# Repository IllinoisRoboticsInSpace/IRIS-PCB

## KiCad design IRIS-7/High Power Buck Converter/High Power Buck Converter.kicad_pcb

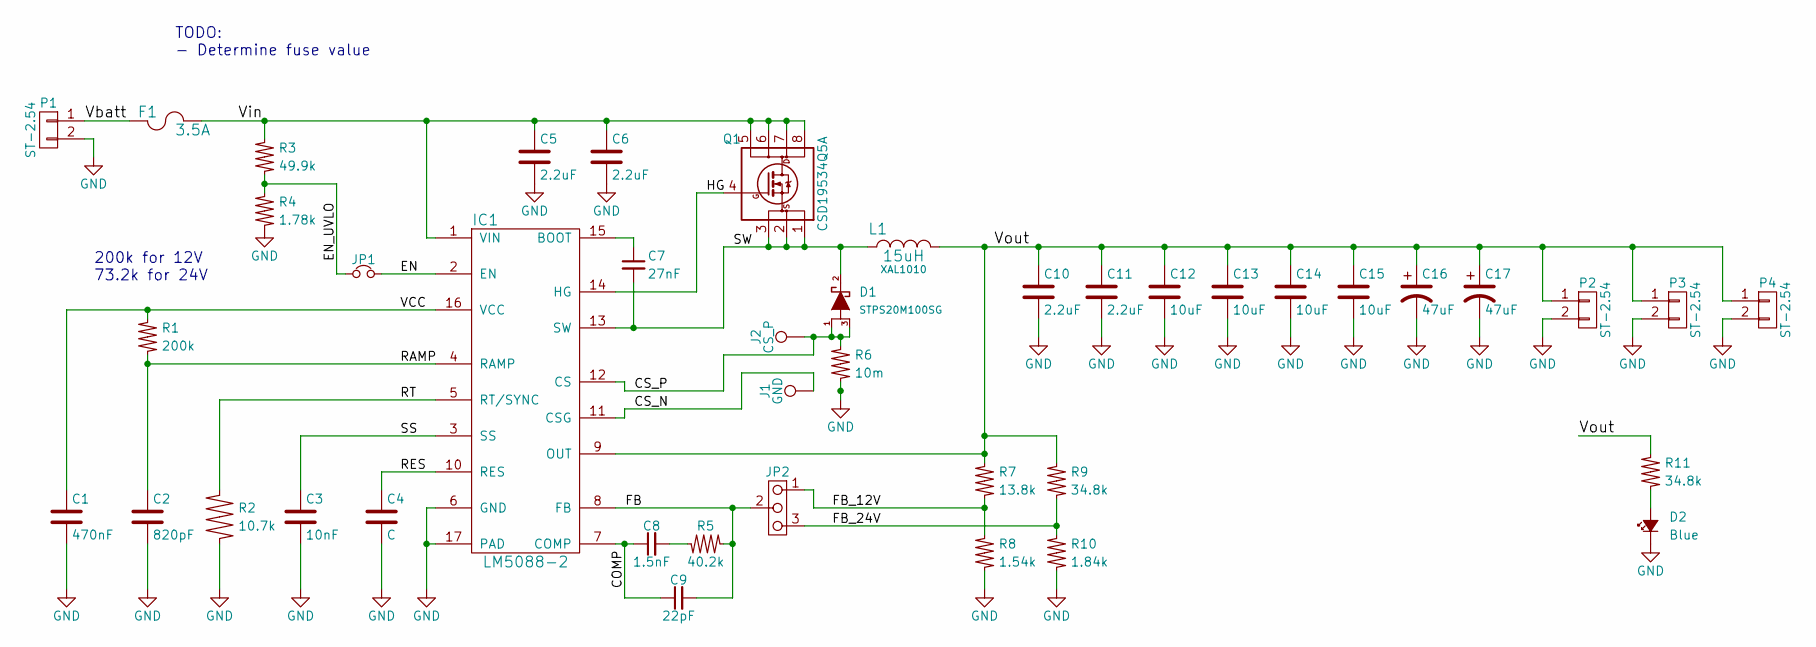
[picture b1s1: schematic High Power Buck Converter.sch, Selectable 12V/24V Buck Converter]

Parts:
C1: 470nF; C_0805
C2: 820pF; C_0805
C3: 10nF; C_0805
C4: C; C_0805
C5, C6, C10, C11: 2.2uF; C_1210
C7: 27nF; C_0805
C8: 1.5nF; C_0805
C9: 22pF; C_0805
C12, C13, C14, C15: 10uF; C_1206
C16, C17: 47uF; CP_Elec_8x10.5
D1: STPS20M100SG; TO-263-3Lead
D2: Blue; LED_0805
F1: 3.5A; Fuseholder5x20_horiz_open_Schurter_0031_8201
IC1: LM5088-2; HTSSOP-16_EP
J1: GND; SMD_0.3
J2: CS_P; SMD_0.3
JP1: JP_NC; Pin_Header_Straight_1x02_Pitch2.54mm
JP2: JP-3_R; Pin_Header_Straight_1x03_Pitch2.54mm
L1: 15uH; XAL1010
P1, P2, P3, P4: ST-2.54; TerminalBlock_Pheonix_MKDS1.5-2pol
Q1: CSD19534Q5A; TDSON-8-1
R1: 200k; R_0805
R2: 10.7k; R_0805
R3: 49.9k; R_0805
R4: 1.78k; R_0805
R5: 40.2k; R_0805
R6: 10m; R_2010
R7: 13.8k; R_0805
R8: 1.54k; R_0805
R9, R11: 34.8k; R_0805
R10: 1.84k; R_0805

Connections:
/COMP: C8.1, C9.1, IC1.7 (COMP)
/CS_N: IC1.11 (CSG), J1.1
/CS_P: D1.1 (A), D1.3 (A), IC1.12 (CS), J2.1, R6.2
/EN: IC1.2 (EN), JP1.2
/EN_UVLO: JP1.1, R3.1, R4.2
/FB: C9.2, IC1.8 (FB), JP2.2, R5.1
/FB_12V: JP2.1, R7.1, R8.2
/FB_24V: JP2.3, R9.1, R10.2
/HG: IC1.14 (HG), Q1.4 (G)
/RAMP: C2.1, IC1.4 (RAMP), R1.1
/RES: C4.1, IC1.10 (RES)
/RT: IC1.5 (RT/SYNC), R2.2
/SS: C3.1, IC1.3 (SS)
/SW: C7.2, D1.2 (K), IC1.13 (SW), L1.1, Q1.1 (S), Q1.2 (S), Q1.3 (S)
/VCC: C1.1, IC1.16 (VCC), R1.2
/Vbatt: F1.1, P1.1
/Vin: C5.1, C6.1, F1.2, IC1.1 (VIN), Q1.5 (D), Q1.6 (D), Q1.7 (D), Q1.8 (D), R3.2
/Vout: C10.1, C11.1, C12.1, C13.1, C14.1, C15.1, C16.1, C17.1, IC1.9 (OUT), L1.2, P2.1, P3.1, P4.1, R7.2, R9.2, R11.2
GND: C1.2, C2.2, C3.2, C4.2, C5.2, C6.2, C10.2, C11.2, C12.2, C13.2, C14.2, C15.2, C16.2, C17.2, D2.1 (K), IC1.6 (GND), IC1.17 (PAD), P1.2, P2.2, P3.2, P4.2, R2.1, R4.1, R6.1, R8.1, R10.1
unnamed: C7.1, IC1.15 (BOOT)
unnamed: C8.2, R5.2
unnamed: D2.2 (A), R11.1

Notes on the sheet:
200k for 12V 73.2k for 24V
TODO: - Determine fuse value

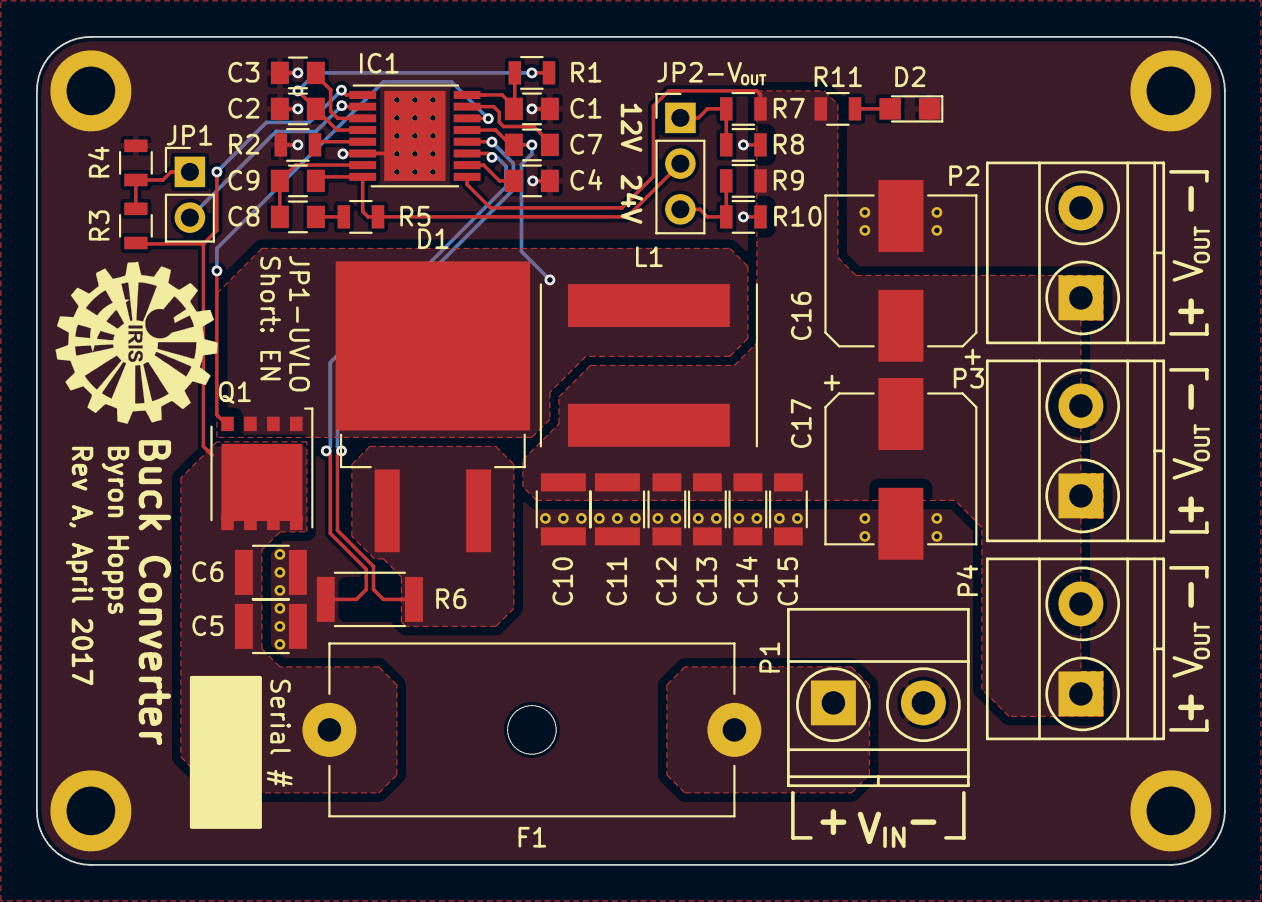
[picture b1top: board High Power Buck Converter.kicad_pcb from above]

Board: 2 copper layers, 66.0 x 46.0 mm, 41 parts (0 on the bottom side), 21 nets.

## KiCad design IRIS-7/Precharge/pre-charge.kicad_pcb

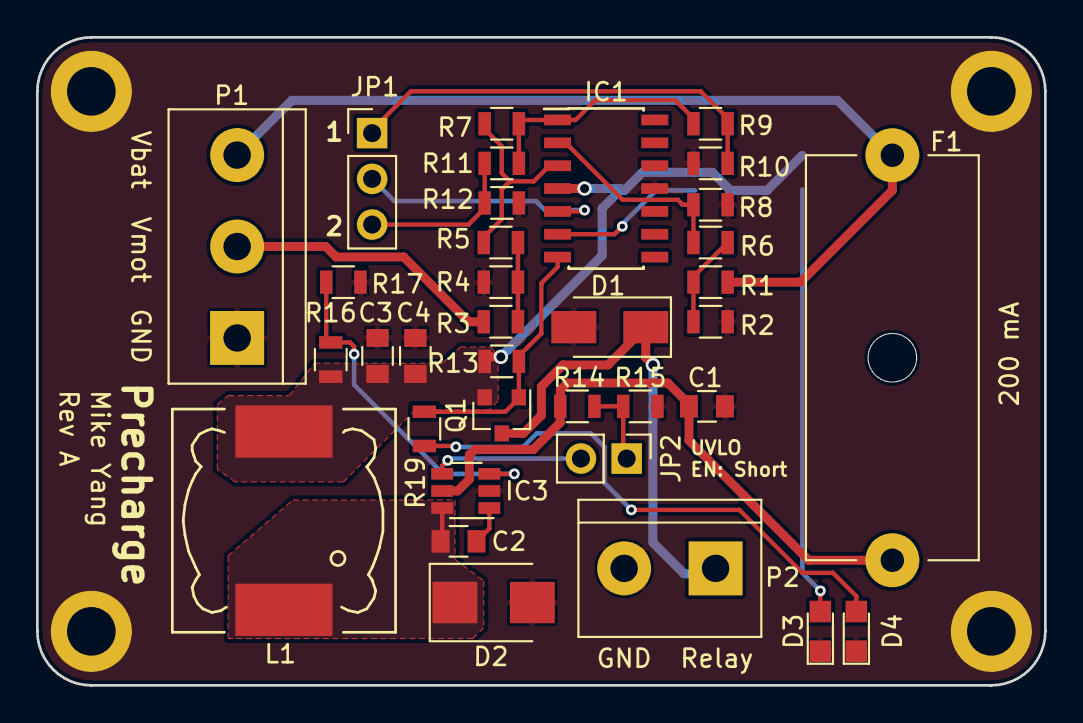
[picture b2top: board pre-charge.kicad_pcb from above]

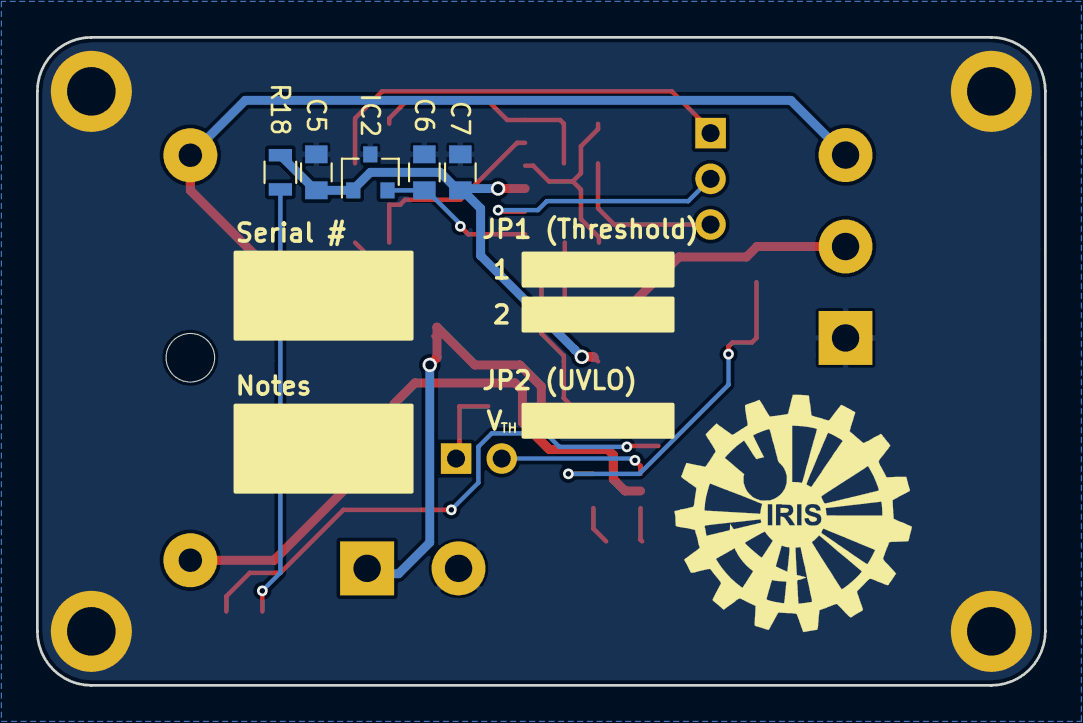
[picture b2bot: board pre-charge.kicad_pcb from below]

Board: 2 copper layers, 56.0 x 36.0 mm, 40 parts (5 on the bottom side), 23 nets.

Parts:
C1: 2.2uF; C_0805
C2, C5, C7: 100nF; C_0805
C3, C4: 4.7uF; C_0805
C6: 1nF; C_0805
D1: SMAJ40CA; D_SMA_Standard
D2: MBRS1100T3G; D_SMB_Standard
D3: Blue; LED_0805
D4: Orange; LED_0805
F1: 0.2A; Fuseholder5x20_horiz_open_Schurter_0031_8201
IC1: LM324; SOIC-14_3.9x8.7mm_Pitch1.27mm
IC2: MAX6001; SOT-23
IC3: LMR16006; TSOT-23-6_MK06A
JP1: JP-3; Socket_Strip_Straight_1x03_Pitch2.54mm
JP2: JP_NC; Socket_Strip_Straight_1x02_Pitch2.54mm
L1: 220uH; Choke_SMD_12x12mm_h8mm
P1: CONN_01X03; bornier3
P2: CONN_01X02; bornier2
Q1: DMP3099L; SOT-23
R1, R3: 270k; R_0805
R2, R4: 51k; R_0805
R5, R6: 12k; R_0805
R7, R8, R10, R11: 100k; R_0805
R9: 27k; R_0805
R12: 15k; R_0805
R13: 1M; R_0805
R14: 620k; R_0805
R15: 20k; R_0805
R16: 88.7k; R_0805
R17: 6.04k; R_0805
R18, R19: 1k; R_0805

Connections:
+12V: C3.1, C4.1, C5.1, C7.1, IC1.4, IC2.1, L1.2, Q1.2, R13.1, R16.2, R18.2
/12V Buck/BOOT: C2.1, IC3.1
/12V Buck/FB: IC3.3, R16.1, R17.2
/12V Buck/SW: C2.2, D2.1, IC3.6, L1.1
/12V Buck/UVLO: JP2.1, R14.1, R15.2
/12V Buck/Vin: C1.1, F1.2, IC3.5, R14.2
/12V Buck/~SHDN: IC3.4, JP2.2
/Relay_Gate: IC1.7, Q1.1, R13.2, R19.2
/Vbat: F1.1, P1.3, R1.1
/Vbdiv: R1.2, R2.1, R6.2
/Vmdiv: R3.2, R4.1, R5.2
/Vmot: P1.2, R3.1
/Vop: IC1.1, R7.2, R9.2, R11.2
/Vref: C6.1, IC1.6, IC2.2
/Vrelay: D1.1, P2.1, Q1.3
GND: C1.2, C3.2, C4.2, C5.2, C6.2, C7.2, D1.2, D2.2, D3.1, D4.1, IC1.11, IC2.3, IC3.2, P1.1, P2.2, R2.2, R4.2, R8.1, R10.1, R12.1, R15.1, R17.1
unnamed: D3.2, R18.1
unnamed: D4.2, R19.1
unnamed: IC1.2, R6.1, R8.2
unnamed: IC1.3, R5.1, R7.1
unnamed: IC1.5, JP1.2
unnamed: JP1.1, R9.1, R10.2
unnamed: JP1.3, R11.1, R12.2

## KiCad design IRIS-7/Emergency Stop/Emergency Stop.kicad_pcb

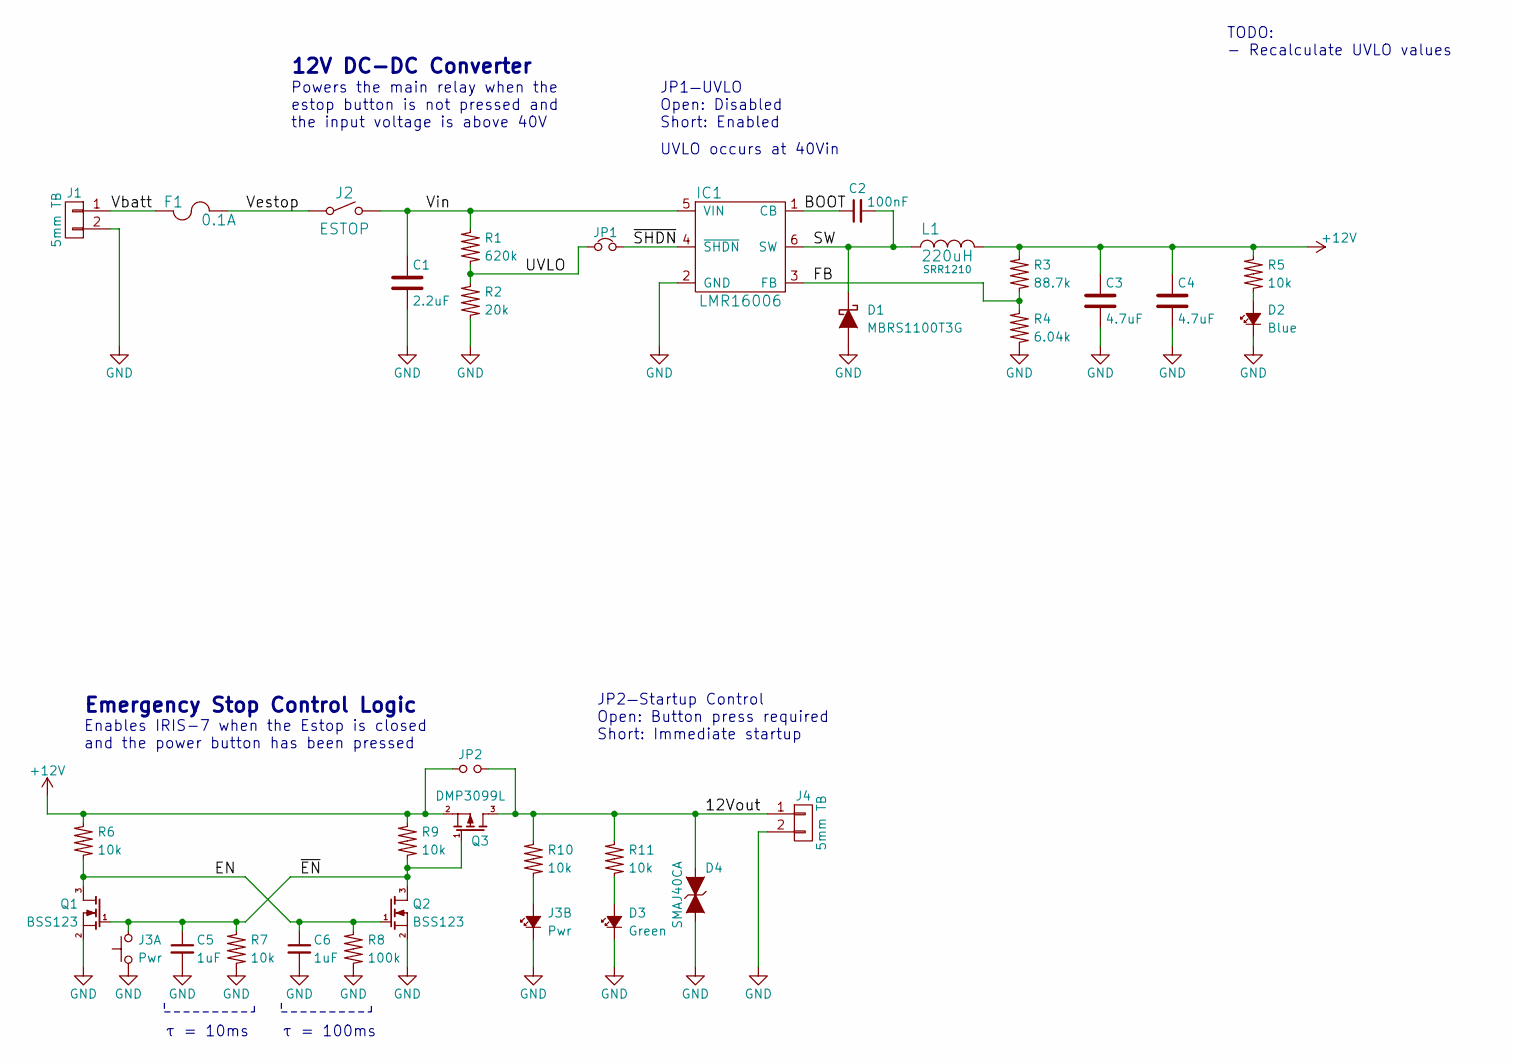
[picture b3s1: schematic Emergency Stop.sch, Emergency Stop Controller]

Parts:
C1: 2.2uF; C_0805
C2: 100nF; C_0805
C3, C4: 4.7uF; C_0805
C5, C6: 1uF; C_0805
D1: MBRS1100T3G; D_SMB_Standard
D2: Blue; LED_0805
D3: Green; LED_0805
D4: SMAJ40CA; D_SMA_Standard
F1: 0.1A; Fuseholder5x20_horiz_open_Schurter_0031_8201
IC1: LMR16006; TSOT-23-6_MK06A
J1, J4: 5mm TB; TerminalBlock_Pheonix_MKDS1.5-2pol
J2: ESTOP; TerminalBlock_Pheonix_MPT-2.54mm_2pol
J3: Pwr; TerminalBlock_Pheonix_MPT-2.54mm_4pol
JP1: JP_NC; Pin_Header_Straight_1x02_Pitch2.54mm
JP2: JP_NO; Pin_Header_Straight_1x02_Pitch2.54mm
L1: 220uH; Choke_SMD_12x12mm_h8mm
Q1, Q2: BSS123; SOT-23
Q3: DMP3099L; SOT-23
R1: 620k; R_0805
R2: 20k; R_0805
R3: 88.7k; R_0805
R4: 6.04k; R_0805
R5, R6, R7, R9, R10, R11: 10k; R_0805
R8: 100k; R_0805

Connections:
+12V: C3.1, C4.1, JP2.1, L1.2, Q3.2 (S), R3.2, R5.2, R6.2, R9.2
/12Vout: D4.1 (K), J4.1, JP2.2, Q3.3 (D), R10.2, R11.2
/BOOT: C2.1, IC1.1 (CB)
/EN: C6.1, Q1.3 (D), Q2.1 (G), R6.1, R8.2
/FB: IC1.3 (FB), R3.1, R4.2
/SW: C2.2, D1.1 (K), IC1.6 (SW), L1.1
/UVLO: JP1.1, R1.1, R2.2
/Vbatt: F1.1, J1.1
/Vestop: F1.2, J2.1 (COM)
/Vin: C1.1, IC1.5 (VIN), J2.2 (NO), R1.2
/~EN: C5.1, J3.2, Q1.1 (G), Q2.3 (D), Q3.1 (G), R7.2, R9.1
/~SHDN: IC1.4 (~SHDN), JP1.2
GND: C1.2, C3.2, C4.2, C5.2, C6.2, D1.2 (A), D2.1 (K), D3.1 (K), D4.2 (A), IC1.2 (GND), J1.2, J3.1, J3.4 (K), J4.2, Q1.2 (S), Q2.2 (S), R2.1, R4.1, R7.1, R8.1
unnamed: D2.2 (A), R5.1
unnamed: D3.2 (A), R11.1
unnamed: J3.3 (A), R10.1

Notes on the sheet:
TODO: - Recalculate UVLO values
JP1—UVLO Open: Disabled Short: Enabled
UVLO occurs at 40Vin
τ = 10ms
τ = 100ms
Emergency Stop Control Logic
Enables IRIS-7 when the Estop is closed and the power button has been pressed
JP2—Startup Control Open: Button press required Short: Immediate startup
12V DC-DC Converter
Powers the main relay when the estop button is not pressed and the input voltage is above 40V

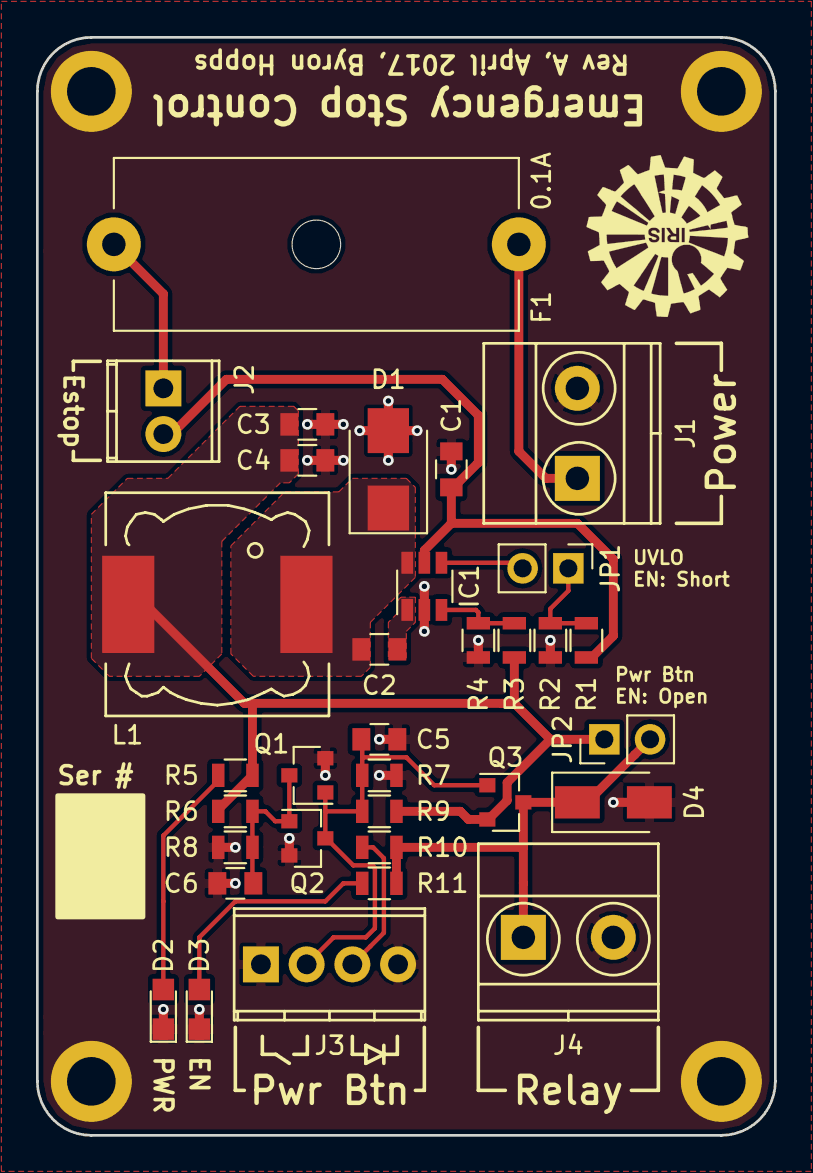
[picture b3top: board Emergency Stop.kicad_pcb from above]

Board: 2 copper layers, 41.0 x 61.0 mm, 33 parts (0 on the bottom side), 16 nets.

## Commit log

2017-03-07 Add submodule for schematic symbol libraries
2017-03-07 Create emergency stop project
    This board delivers power to the main relay when the
    emergency stop button is pressed
2017-03-07 Setup the 12V buck converter
2017-03-08 Add startup control to schematic
    Schematic is now ready for layout
2017-03-08 Complete component placement
2017-03-08 Adjust wires in schematic
2017-03-09 Complete most of the routing
2017-03-09 Clean up copper zones
2017-03-14 Adjust trace positioning
2017-04-13 Add more libraries to project
2017-04-20 Initial commit for high power buck converter
2017-04-21 Begin assiging footprints to schematic symbols
2017-04-21 Created footprint for main inductor
2017-04-21 Update Symbol Libraries with new parts
2017-04-21 Begin footprint for LM5088-2
2017-04-22 Finish assigning part footprints
2017-04-22 Begin component placement
2017-04-24 Import precharge design files
2017-04-24 Update symbol libraries
2017-04-24 Import IRIS_Logos library
2017-04-24 Minor tweaks before OK2FAB
2017-04-24 Add gerber files to gitignore
2017-04-24 Finalize board design for Rev A release
2017-04-24 Update power routing
2017-04-24 Make final changes before fab release
2017-04-25 Finish layout and final tweaks
